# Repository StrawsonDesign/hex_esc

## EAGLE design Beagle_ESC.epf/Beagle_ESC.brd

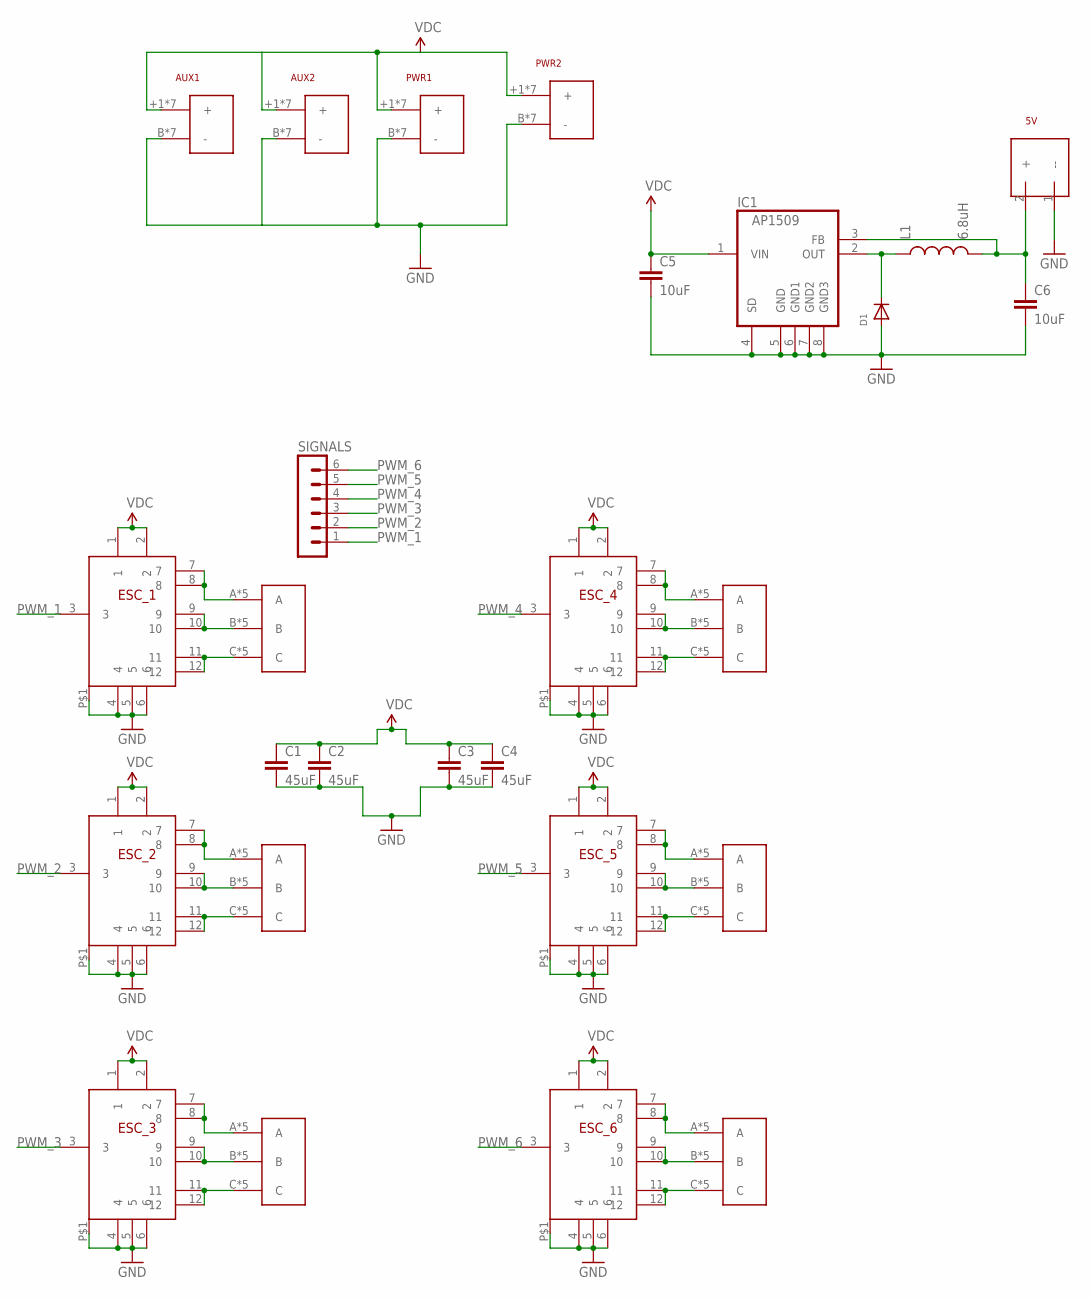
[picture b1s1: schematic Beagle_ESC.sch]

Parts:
1, 2, 3, 4, 5, 6: 3_PADS
5V: HEADER_PWR
AUX1, AUX2: 2PADS
C1, C2, C3, C4: 45uF; 1206
C5, C6: 10uF; 0805
D1: DIODESOD-123; SOD-123
ESC_1, ESC_2, ESC_3, ESC_4, ESC_5, ESC_6: DYS_BLHELI_ESC
IC1: AP1509SOIC-8-TIGHT; SO08-TIGHT
L1: 6.8uH; TAIYO_NRS
PWR1, PWR2: 2PADS
SIGNALS: MA06-1

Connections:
1A: 1.A, 1.P$4 (A), 1.P$7 (A), 1.P$8 (A), 1.P$9 (A), ESC_1.7, ESC_1.8
1B: 1.B, 1.P$5 (B), 1.P$10 (B), 1.P$11 (B), 1.P$12 (B), ESC_1.9, ESC_1.10
1C: 1.C, 1.P$6 (C), 1.P$13 (C), 1.P$14 (C), 1.P$15 (C), ESC_1.11, ESC_1.12
2A: 2.A, 2.P$4 (A), 2.P$7 (A), 2.P$8 (A), 2.P$9 (A), ESC_2.7, ESC_2.8
2B: 2.B, 2.P$5 (B), 2.P$10 (B), 2.P$11 (B), 2.P$12 (B), ESC_2.9, ESC_2.10
2C: 2.C, 2.P$6 (C), 2.P$13 (C), 2.P$14 (C), 2.P$15 (C), ESC_2.11, ESC_2.12
3A: 3.A, 3.P$4 (A), 3.P$7 (A), 3.P$8 (A), 3.P$9 (A), ESC_3.7, ESC_3.8
3B: 3.B, 3.P$5 (B), 3.P$10 (B), 3.P$11 (B), 3.P$12 (B), ESC_3.9, ESC_3.10
3C: 3.C, 3.P$6 (C), 3.P$13 (C), 3.P$14 (C), 3.P$15 (C), ESC_3.11, ESC_3.12
4A: 4.A, 4.P$4 (A), 4.P$7 (A), 4.P$8 (A), 4.P$9 (A), ESC_4.7, ESC_4.8
4B: 4.B, 4.P$5 (B), 4.P$10 (B), 4.P$11 (B), 4.P$12 (B), ESC_4.9, ESC_4.10
4C: 4.C, 4.P$6 (C), 4.P$13 (C), 4.P$14 (C), 4.P$15 (C), ESC_4.11, ESC_4.12
5A: 5.A, 5.P$4 (A), 5.P$7 (A), 5.P$8 (A), 5.P$9 (A), ESC_5.7, ESC_5.8
5B: 5.B, 5.P$5 (B), 5.P$10 (B), 5.P$11 (B), 5.P$12 (B), ESC_5.9, ESC_5.10
5C: 5.C, 5.P$6 (C), 5.P$13 (C), 5.P$14 (C), 5.P$15 (C), ESC_5.11, ESC_5.12
6A: 6.A, 6.P$4 (A), 6.P$7 (A), 6.P$8 (A), 6.P$9 (A), ESC_6.7, ESC_6.8
6B: 6.B, 6.P$5 (B), 6.P$10 (B), 6.P$11 (B), 6.P$12 (B), ESC_6.9, ESC_6.10
6C: 6.C, 6.P$6 (C), 6.P$13 (C), 6.P$14 (C), 6.P$15 (C), ESC_6.11, ESC_6.12
GND: 5V.1 (--), AUX1.B (-), AUX1.P$5 (-), AUX1.P$10 (-), AUX1.P$11 (-), AUX1.P$12 (-), AUX1.P$13 (-), AUX1.P$14 (-), AUX2.B (-), AUX2.P$5 (-), AUX2.P$10 (-), AUX2.P$11 (-), AUX2.P$12 (-), AUX2.P$13 (-), AUX2.P$14 (-), C1.2, C2.2, C3.2, C4.2, C5.2, C6.2, D1.A, ESC_1.4, ESC_1.5, ESC_1.6, ESC_1.P$1, ESC_2.4, ESC_2.5, ESC_2.6, ESC_2.P$1, ESC_3.4, ESC_3.5, ESC_3.6, ESC_3.P$1, ESC_4.4, ESC_4.5, ESC_4.6, ESC_4.P$1, ESC_5.4, ESC_5.5, ESC_5.6, ESC_5.P$1, ESC_6.4, ESC_6.5, ESC_6.6, ESC_6.P$1, IC1.4 (SD), IC1.5 (GND), IC1.6 (GND1), IC1.7 (GND2), IC1.8 (GND3), PWR1.B (-), PWR1.P$5 (-), PWR1.P$10 (-), PWR1.P$11 (-), PWR1.P$12 (-), PWR1.P$13 (-), PWR1.P$14 (-), PWR2.B (-), PWR2.P$5 (-), PWR2.P$10 (-), PWR2.P$11 (-), PWR2.P$12 (-), PWR2.P$13 (-), PWR2.P$14 (-)
unnamed: D1.C, IC1.2 (OUT), L1.1
unnamed: 5V.2 (+), C6.1, IC1.3 (FB), L1.2
PWM_1: ESC_1.3, SIGNALS.1
PWM_2: ESC_2.3, SIGNALS.2
PWM_3: ESC_3.3, SIGNALS.3
PWM_4: ESC_4.3, SIGNALS.4
PWM_5: ESC_5.3, SIGNALS.5
PWM_6: ESC_6.3, SIGNALS.6
VCC: AUX1.+1 (+), AUX1.+2 (+), AUX1.+3 (+), AUX1.+4 (+), AUX1.+5 (+), AUX1.+BOTTOM (+), AUX1.+TOP (+), AUX2.+1 (+), AUX2.+2 (+), AUX2.+3 (+), AUX2.+4 (+), AUX2.+5 (+), AUX2.+BOTTOM (+), AUX2.+TOP (+), C1.1, C2.1, C3.1, C4.1, C5.1, ESC_1.1, ESC_1.2, ESC_2.1, ESC_2.2, ESC_3.1, ESC_3.2, ESC_4.1, ESC_4.2, ESC_5.1, ESC_5.2, ESC_6.1, ESC_6.2, IC1.1 (VIN), PWR1.+1 (+), PWR1.+2 (+), PWR1.+3 (+), PWR1.+4 (+), PWR1.+5 (+), PWR1.+BOTTOM (+), PWR1.+TOP (+), PWR2.+1 (+), PWR2.+2 (+), PWR2.+3 (+), PWR2.+4 (+), PWR2.+5 (+), PWR2.+BOTTOM (+), PWR2.+TOP (+)

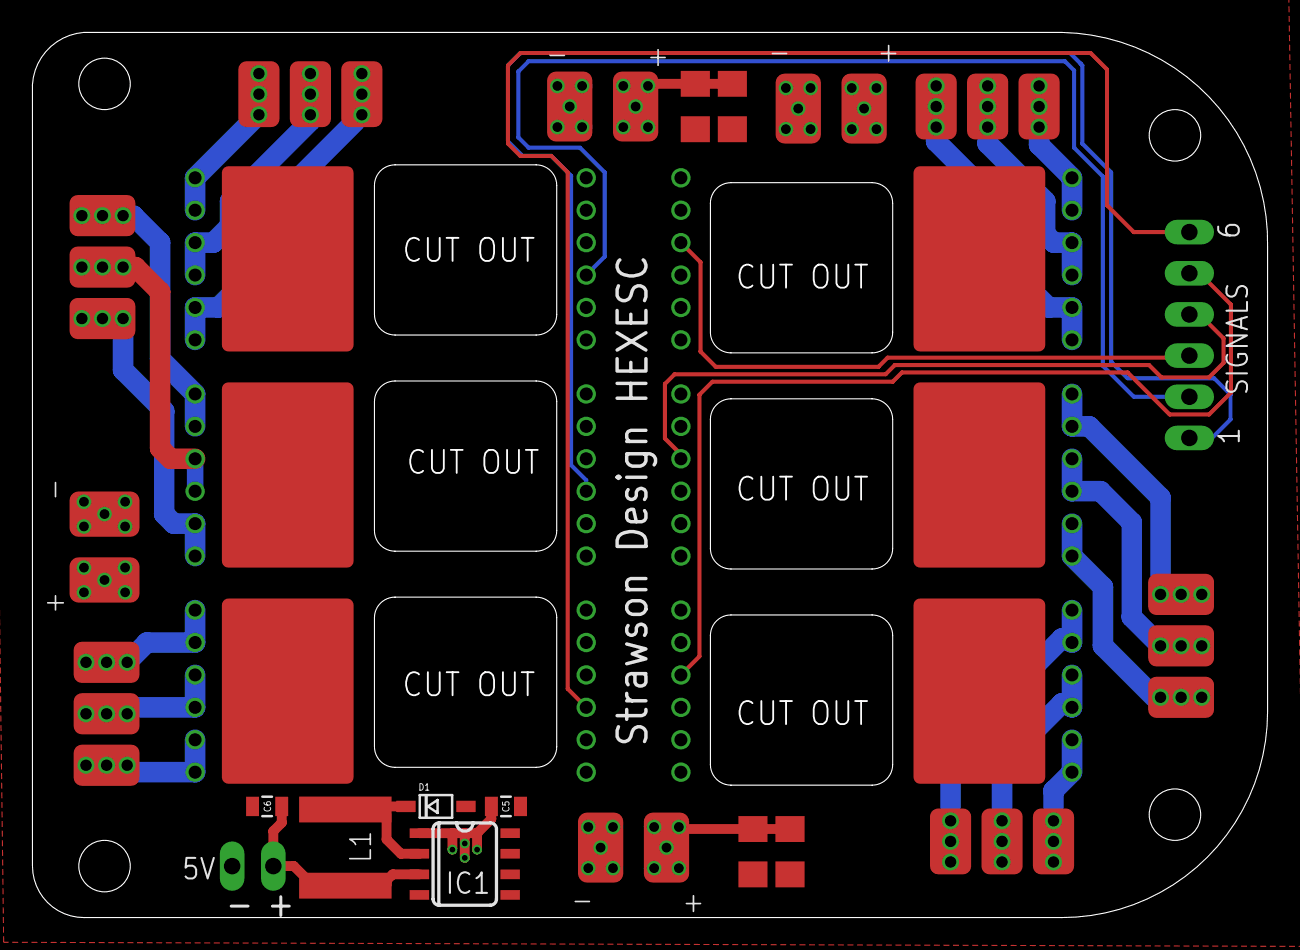
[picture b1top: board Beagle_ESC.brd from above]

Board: 2 copper layers, 76.2 x 54.6 mm, 27 parts (0 on the bottom side), 28 nets.
